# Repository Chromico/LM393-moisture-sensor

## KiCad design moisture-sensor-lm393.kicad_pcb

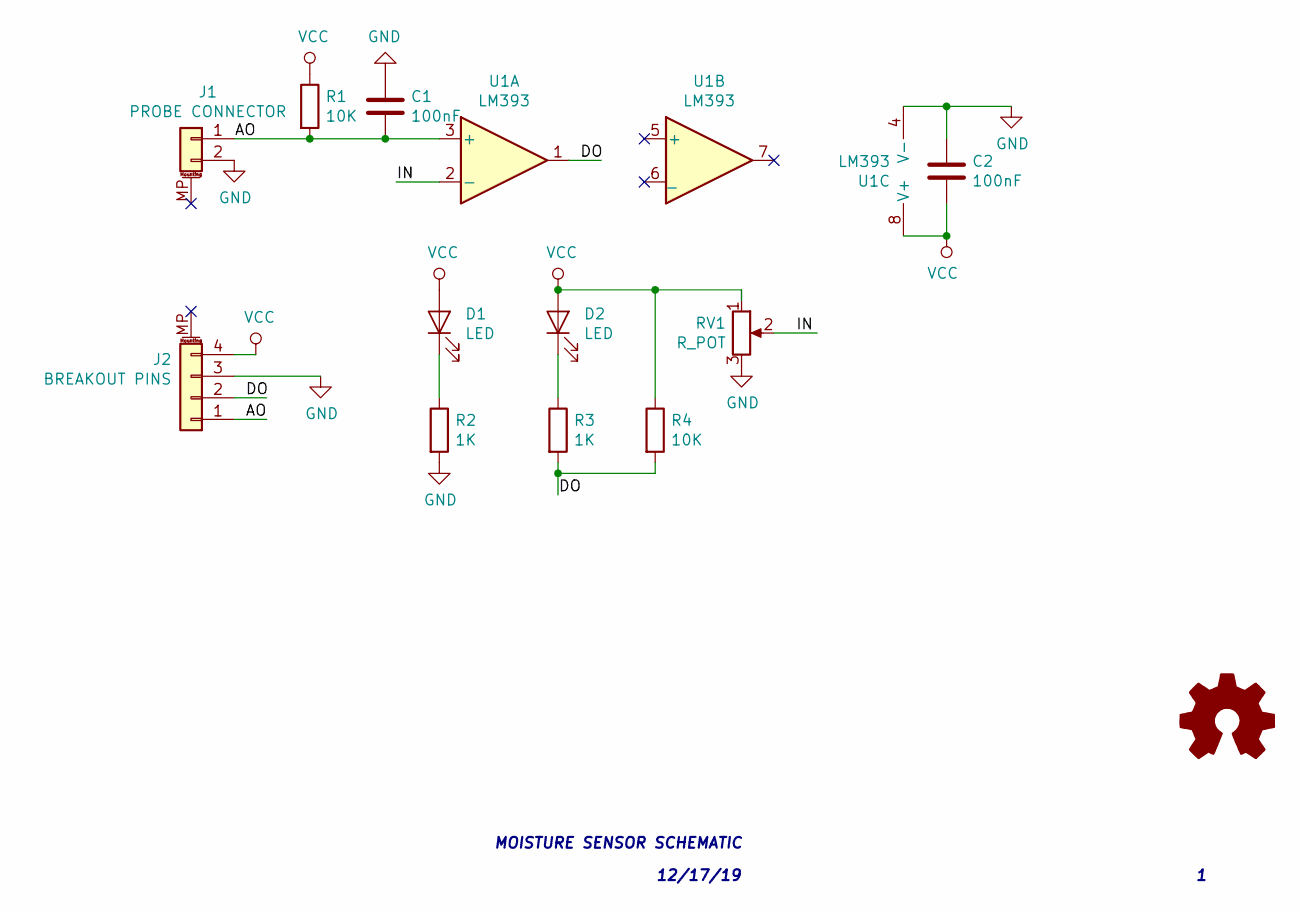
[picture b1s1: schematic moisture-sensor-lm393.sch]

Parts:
C1, C2: 100nF
D1, D2: LED
J1: PROBE CONNECTOR
J2: BREAKOUT PINS
R1, R4: 10K
R2, R3: 1K
RV1: R_POT
U1: LM393

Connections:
/AO: C1.2, J1.1, J2.1, R1.2, U1.3 (+)
/DO: J2.2, R3.2, R4.2, U1.1
/IN: RV1.2, U1.2 (-)
GND: C1.1, C2.1, J1.2, J2.3, R2.2, RV1.3, U1.4 (V-)
unnamed: D1.1 (K), R2.1
unnamed: D2.1 (K), R3.1
VCC: C2.2, D1.2 (A), D2.2 (A), J2.4, R1.1, R4.1, RV1.1, U1.8 (V+)

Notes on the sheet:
MOISTURE SENSOR SCHEMATIC
12/17/19

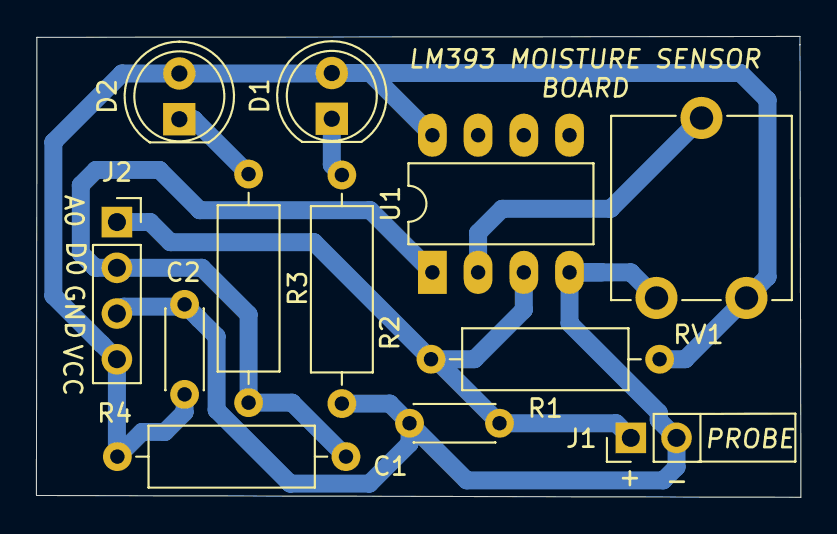
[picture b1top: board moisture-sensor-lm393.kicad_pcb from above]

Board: 2 copper layers, 42.5 x 25.6 mm, 12 parts (0 on the bottom side), 7 nets.
